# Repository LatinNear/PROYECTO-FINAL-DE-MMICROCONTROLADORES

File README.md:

# PROYECTO-FINAL-DE-MMICROCONTROLADORES

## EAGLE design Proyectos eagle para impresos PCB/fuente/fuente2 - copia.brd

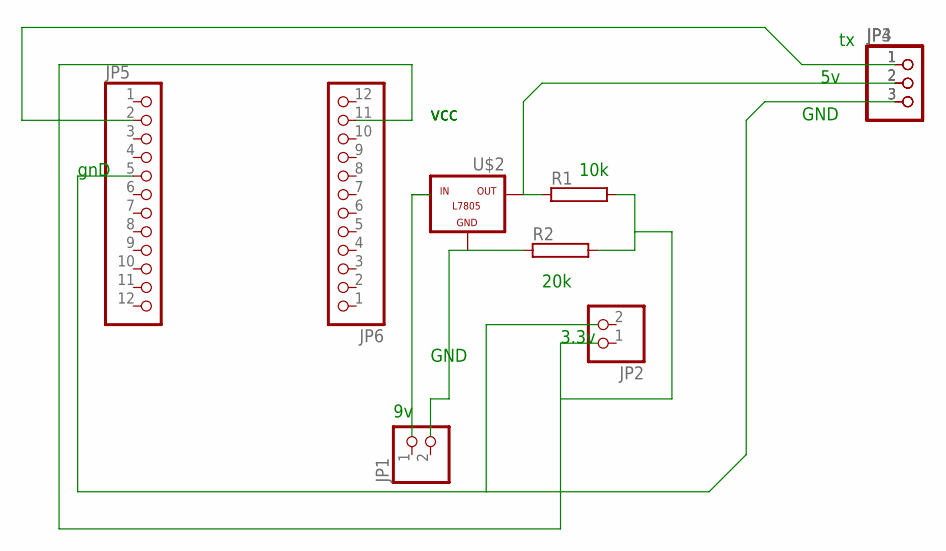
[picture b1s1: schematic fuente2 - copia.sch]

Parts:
JP1, JP2: PINHD-1X2; 1X02
JP3, JP4: PINHD-1X3; 1X03
JP5, JP6: PINHD-1X12; 1X12
R1, R2: RCA4050; CA4050
U$2: -L7805; L7805

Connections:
unnamed: R2.1, U$2.GND
unnamed: JP3.1, JP4.1, JP5.2
unnamed: JP3.2, JP4.2, R1.1, U$2.OUT
unnamed: JP6.11, R1.2, R2.2
unnamed: JP3.3, JP4.3, JP5.5

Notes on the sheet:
GND
20k
10k
3.3v
vcc
gnD

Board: 2 copper layers, 9 parts (0 on the bottom side), 5 nets, no tracks yet.

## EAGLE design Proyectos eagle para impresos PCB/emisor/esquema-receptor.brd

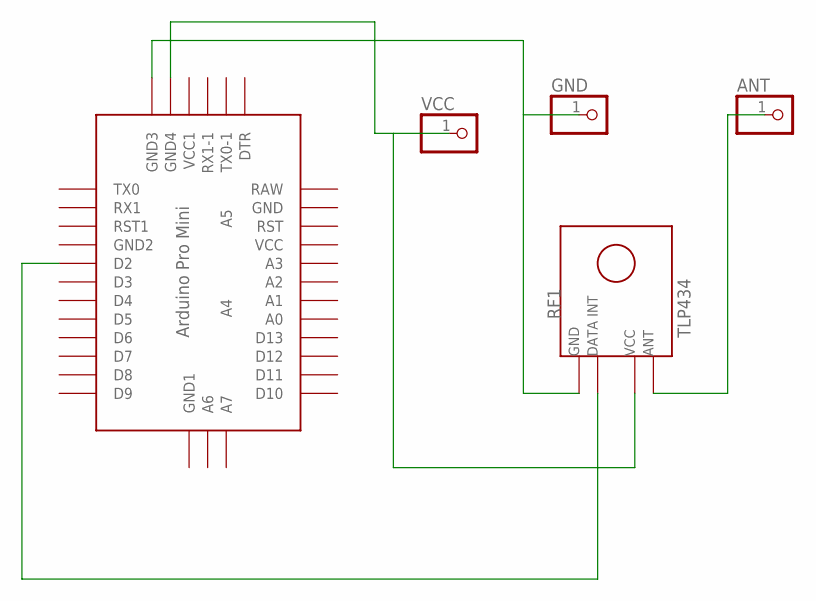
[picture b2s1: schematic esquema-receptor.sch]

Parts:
ANT: PINHD-1X1; 1X01
GND: PINHD-1X1; 1X01
RF1: TLP434
U$1: ABK-PRO-MINI
VCC: PINHD-1X1; 1X01

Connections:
ANT: ANT.1, RF1.4
GND: GND.1, RF1.1, U$1.GND2 (GND3)
unnamed: RF1.2, U$1.D2
VCC: RF1.3, U$1.GND3 (GND4), VCC.1

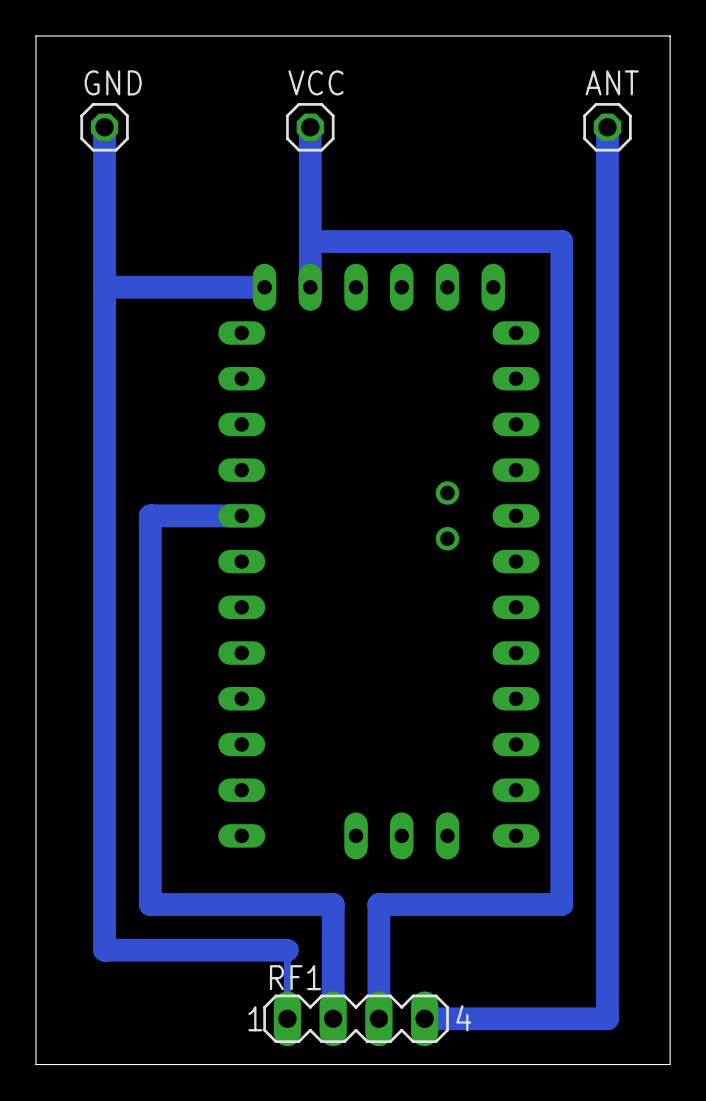
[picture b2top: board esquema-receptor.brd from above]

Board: 2 copper layers, 35.2 x 57.1 mm, 5 parts (0 on the bottom side), 4 nets.

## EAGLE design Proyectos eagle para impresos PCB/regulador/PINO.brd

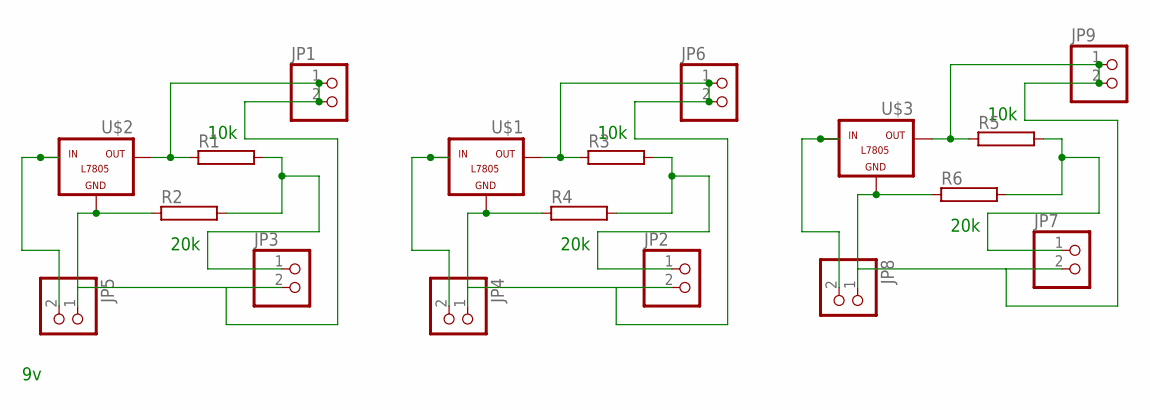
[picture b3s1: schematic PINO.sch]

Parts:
JP1, JP2, JP3, JP4, JP5, JP6, JP7, JP8, JP9: PINHD-1X2M; 1X02M
R1, R2, R3, R4, R5, R6: RCA4050; CA4050
U$1, U$2, U$3: -L7805; L7805

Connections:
unnamed: JP5.2, U$2.IN
unnamed: JP1.1, JP1.2, JP3.2, JP5.1, R1.1, R2.1, U$2.GND, U$2.OUT
unnamed: JP4.2, U$1.IN
unnamed: JP2.1, R3.2, R4.2
unnamed: JP3.1, R1.2, R2.2
unnamed: JP2.2, JP4.1, JP6.1, JP6.2, R3.1, R4.1, U$1.GND, U$1.OUT
unnamed: JP8.2, U$3.IN
unnamed: JP7.1, R5.2, R6.2
unnamed: JP7.2, JP8.1, JP9.1, JP9.2, R5.1, R6.1, U$3.GND, U$3.OUT

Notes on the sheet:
20k
10k

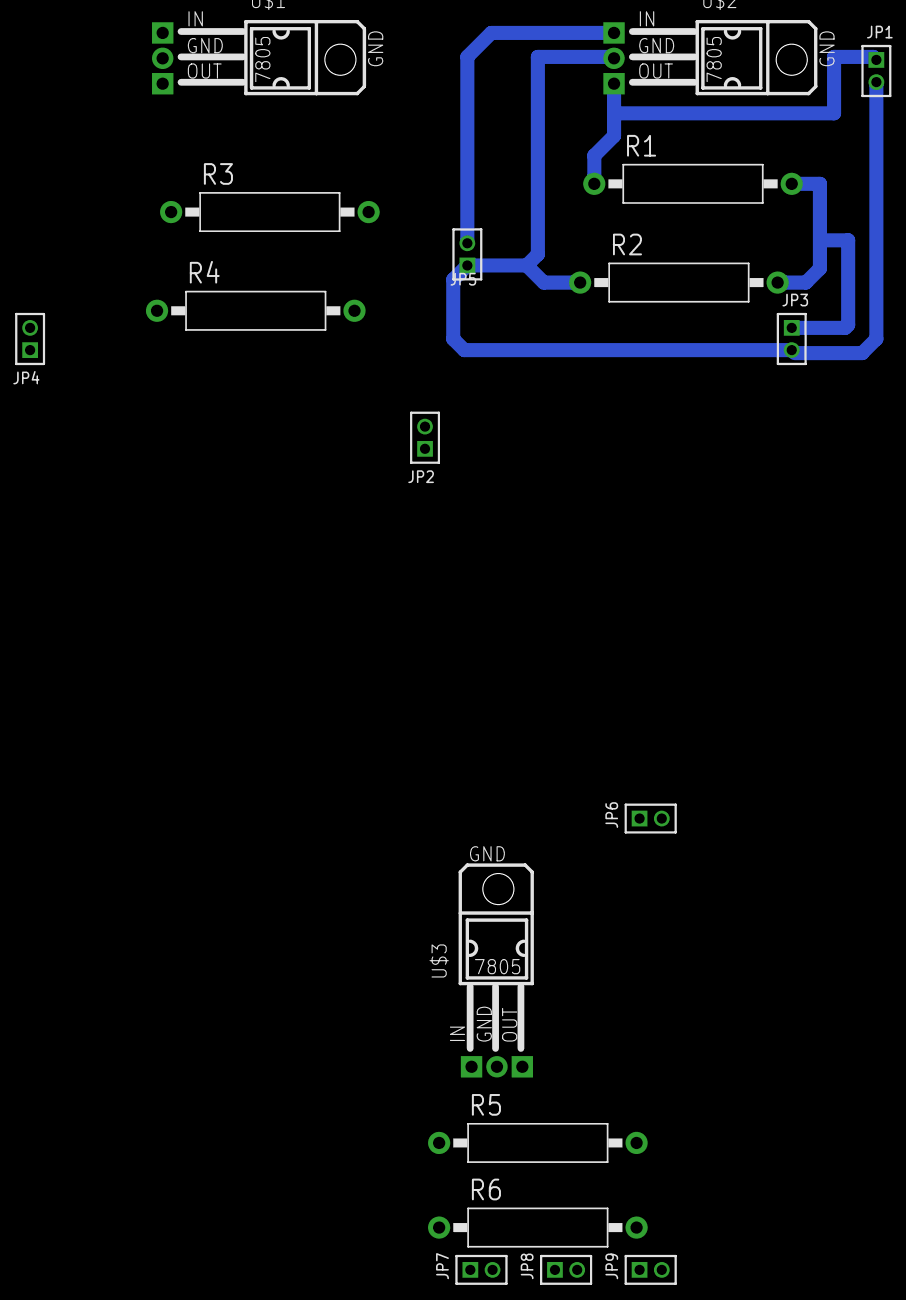
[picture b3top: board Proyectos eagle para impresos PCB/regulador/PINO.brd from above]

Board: 2 copper layers, 18 parts (0 on the bottom side), 9 nets.

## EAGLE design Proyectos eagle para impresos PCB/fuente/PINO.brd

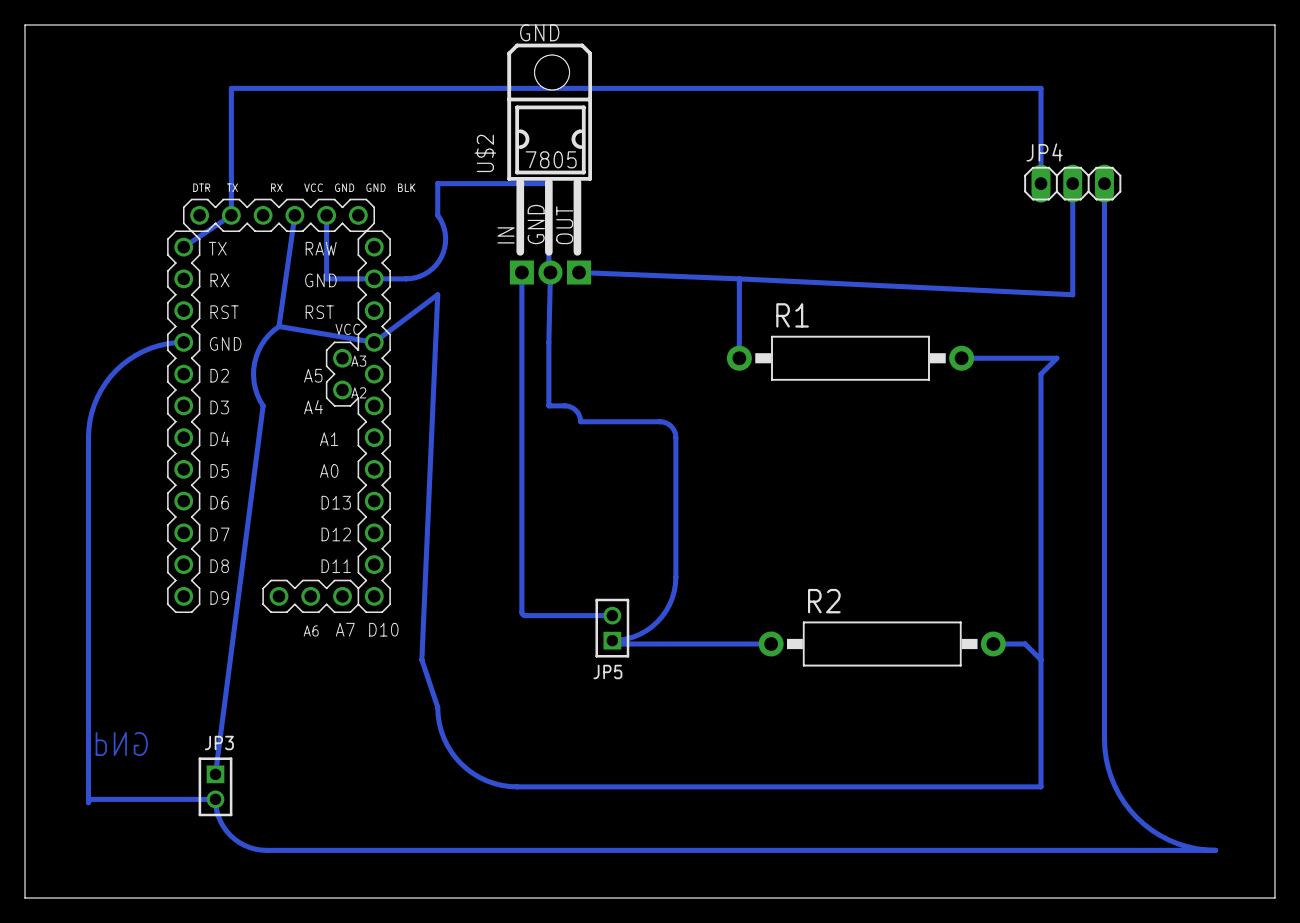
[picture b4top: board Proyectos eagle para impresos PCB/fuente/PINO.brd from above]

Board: 2 copper layers, 100.0 x 69.8 mm, 7 parts (0 on the bottom side), 5 nets.

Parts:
ARDUINO1: ARDUINO_PRO_MINI
JP3, JP5: 1X02M
JP4: 1X03
R1, R2: CA4050
U$2: -L7805; L7805

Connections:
unnamed: JP5.2, U$2.IN
unnamed: ARDUINO1.GND, ARDUINO1.GND@1, ARDUINO1.GND@2, ARDUINO1.GND@3, JP3.2, JP4.3, JP5.1, R2.1, U$2.GND
unnamed: ARDUINO1.DTR, ARDUINO1.TX, ARDUINO1.TX@1, JP4.1
unnamed: ARDUINO1.VCC, ARDUINO1.VCC@1, JP3.1, R1.2, R2.2
unnamed: JP4.2, R1.1, U$2.OUT
